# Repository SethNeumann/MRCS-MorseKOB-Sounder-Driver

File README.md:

# REPO NAME: MRCS-MorseKOB-Sounder-Driver
## License: Creative Commons Attribution-NonCommercial-ShareAlike

A simple interface board to drive a vintage telegraph sounder from an RS232 Dongle for the popular MorseKOB program

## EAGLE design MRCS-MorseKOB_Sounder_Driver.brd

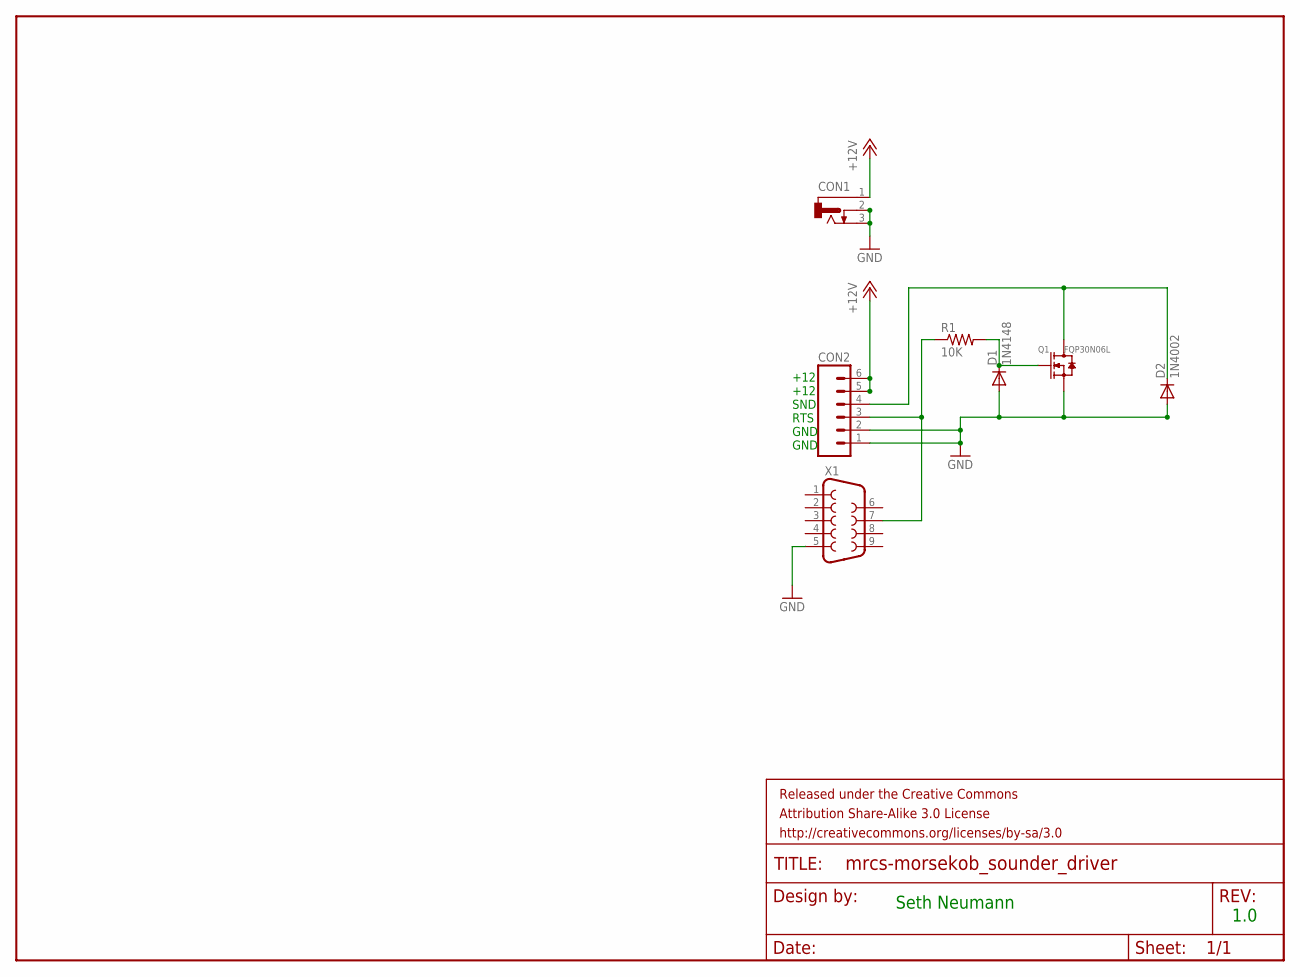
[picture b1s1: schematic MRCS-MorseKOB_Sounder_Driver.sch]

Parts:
CON1: CONNECTOR-DC-POWER-RA; DCJ0202
CON2: CONNECTOR-M063.5MM-6; SCREWTERMINAL-3.5MM-6
D1: 1N4148; DIODE-1N4148
D2: 1N4002; DIODE-1N4001
FRAME1: FRAME-LETTER; CREATIVE_COMMONS
Q1: FQP30N06L; TO220V
R1: 10K; AXIAL-0.4-RES
X1: DB9FEMALE; DB9

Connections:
+12V: CON1.1, CON2.5, CON2.6
GND: CON1.2, CON1.3, CON2.1, CON2.2, D1.A, D2.A, Q1.3 (S), X1.5
unnamed: CON2.3, R1.P$1 (1), X1.7
unnamed: D1.C, Q1.1 (G), R1.P$2 (2)
unnamed: CON2.4, D2.C, Q1.2 (D)

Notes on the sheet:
+12 +12 SND RTS GND GND
Seth Neumann
1.0

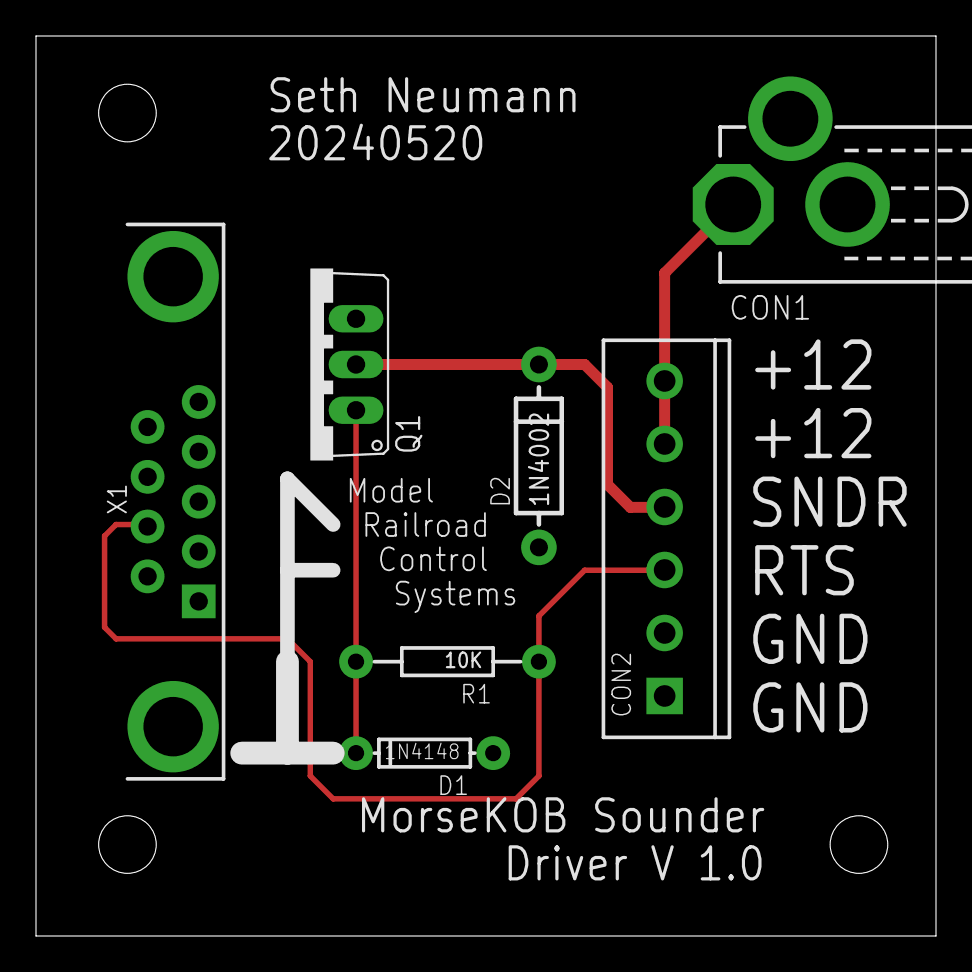
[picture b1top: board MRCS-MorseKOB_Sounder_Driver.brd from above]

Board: 2 copper layers, 50.0 x 50.0 mm, 10 parts (0 on the bottom side), 5 nets.

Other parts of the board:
U$1: MRCS-LOGO
U$2: CA-PROP65WARNING

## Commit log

2024-06-01 Update DESCRIPTION
2024-06-01 Update INFO
2024-06-01 migrated off line files into repository
    Moved work done off line including some documentation into the repo. Initial design was successful. Not surprising as I used the schematic in the excellent MorseKOB documentation.
2024-06-01 removed the large documentation files
2024-06-01 moving files for set up
2024-06-03 finished Version 1.0 documentation

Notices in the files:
parts and their libraries:
SparkFun-Connectors: Licensing: CC v3.0 Share-Alike You are welcome to use this library for commercial purposes.
SparkFun-Aesthetics: Released under the Creative Commons Attribution Share-Alike 3.0 License
SparkFun-Aesthetics: http://creativecommons.org/licenses/by-sa/3.0
